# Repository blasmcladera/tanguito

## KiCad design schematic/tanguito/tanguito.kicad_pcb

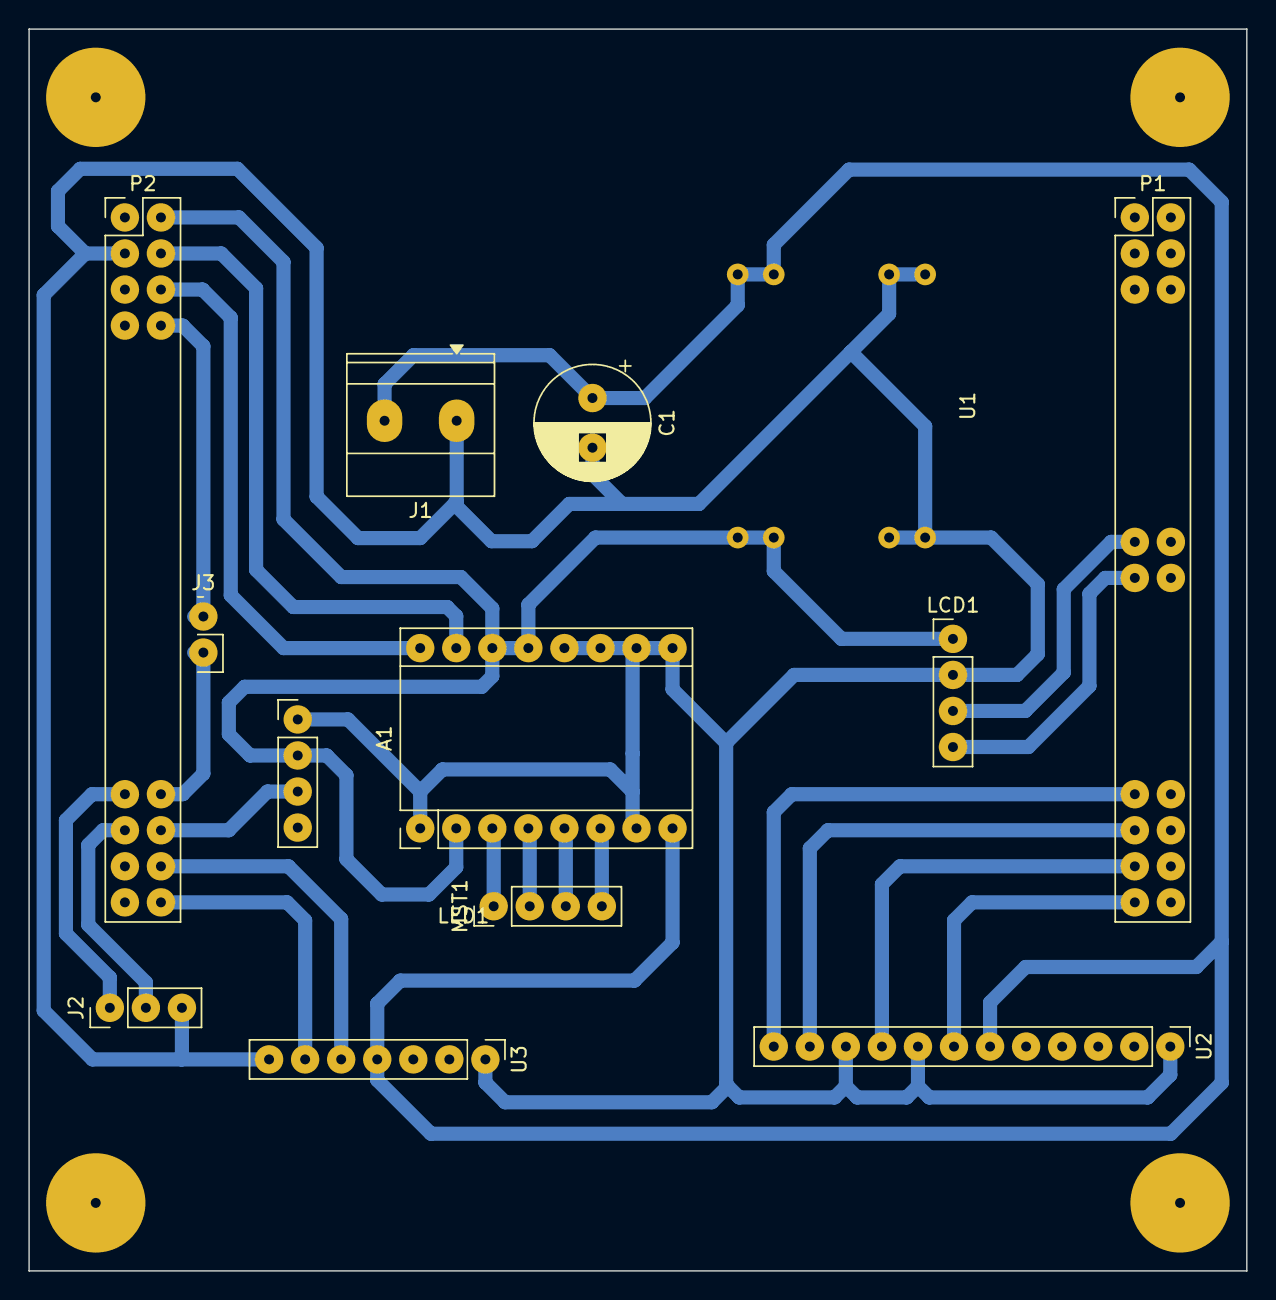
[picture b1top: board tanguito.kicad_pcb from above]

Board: 2 copper layers, 85.8 x 87.5 mm, 13 parts (0 on the bottom side), 22 nets.

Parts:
A1: A4988; Pololu_Breakout-16_15.2x20.3mm
C1: 100uF; CP_Radial_D8.0mm_P3.50mm
J1: Barrel_Jack; TerminalBlock_Phoenix_MKDS-1,5-2-5.08_1x02_P5.08mm_Horizont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
J2: Botones; PinHeader_1x03_P2.54mm_Vertical
J3: Botones; PinHeader_1x02_P2.54mm_Vertical
LCD1: PinHeader_1x04_P2.54mm_Vertical
LED1: PinHeader_1x04_P2.54mm_Vertical
MST1: Stepper Motor; PinHeader_1x04_P2.54mm_Vertical
P1, P2: PinHeader_2x20_P2.54mm_Vertical
U1: MP1584_Module; MP1584_Module_TodoMicro_22x17
U2: L298N; PinHeader_1x12_P2.54mm_Vertical
U3: L298N; PinHeader_1x07_P2.54mm_Vertical

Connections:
+5V: A1.2 (VDD), A1.13 (~RESET), A1.14 (~SLEEP), LCD1.1 (VCC), LED1.2 (VCC), P2.2 (5V), U1.4 (VOUT+)
+12V: A1.8 (VMOT), C1.1, J1.2, U1.1 (VIN+), U2.6 (Vs), U3.4 (Vs)
/ENET_MDC: J3.1, P2.8 (MDC)
/ENET_RXD1: A1.15 (STEP), P2.4 (RXD1)
/ENET_TXEN: A1.16 (DIR), P2.6 (TX_EN)
/GPIO3: J3.2, P2.34 (GPIO3)
/GPIO4: J2.1, P2.33 (GPIO4)
/GPIO5: LED1.3 (DI), P2.36 (GPIO5)
/GPIO6: J2.2, P2.35 (GPIO6)
/GPIO7: P2.38 (GPIO7), U3.5 (IN1)
/GPIO8: P2.40 (GPIO8), U3.6 (EnA)
/I2C_SCL: LCD1.4 (SCL), P1.21 (I2C_SCL)
/I2C_SDA: LCD1.3 (SDA), P1.19 (I2C_SCA)
/MST 1A: A1.4 (1A), MST1.2 (-_2)
/MST 1B: A1.3 (1B), MST1.1
/MST 2A: A1.5 (2A), MST1.3
/MST 2B: A1.6 (2B), MST1.4
/PWM3: P1.37 (T_FL2), U2.9 (EnA)
/PWM4: P1.35 (T_FL3), U2.11 (EnB)
/T_COL0: P1.39 (T_COL0), U2.7 (IN1)
/T_FIL0: P1.33 (T_FL0), U2.12 (IN4)
GND: A1.1 (GND), A1.7 (GND), A1.9 (~ENABLE), A1.10 (MS1), A1.11 (MS2), A1.12 (MS3), C1.2, J1.1, J2.3, LCD1.2 (GND), LED1.1 (GND), P2.3 (GND), U1.2 (VIN-), U1.3 (VOUT-), U2.1 (GND), U2.8 (IN2), U2.10 (IN3), U3.1 (GND), U3.7 (IN2)
